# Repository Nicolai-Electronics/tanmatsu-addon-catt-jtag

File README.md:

# Tanmatsu add-on: CATT to JTAG

This repository contains the hardware design files for the CATT to JTAG adapter.

## Documentation

Need the schematic? [It's in this repository as a PDF file](schematic.pdf).

## License

This hardware design may be used under the terms of the [CERN-OHL-P](LICENSE) license.

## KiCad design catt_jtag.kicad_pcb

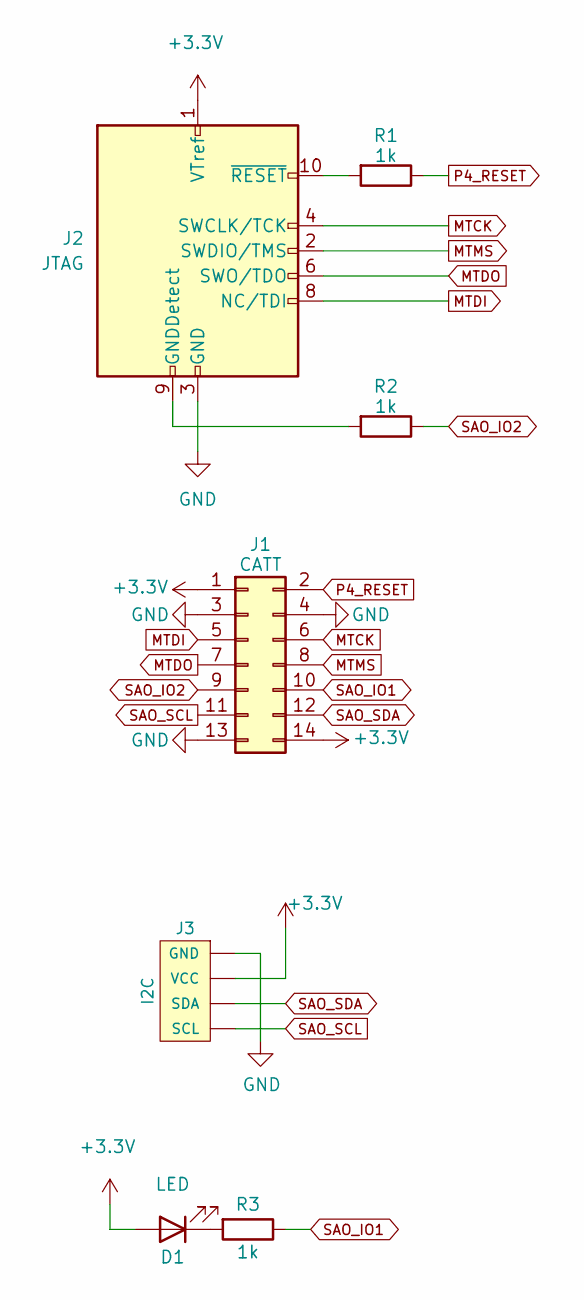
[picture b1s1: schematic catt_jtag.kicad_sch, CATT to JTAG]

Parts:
D1: LED; LED_0603_1608Metric; LCSC C7496820
J1: CATT; PinHeader_2x07_P2.54mm_Horizontal; LCSC C492435
J2: JTAG; CONN-TH_3130-10SG0BK00T1; LCSC C42372547
J3: I2C; 1X04_1MM_RA_GND; LCSC C7433425
R1, R2, R3: 1k; R_0402_1005Metric; LCSC C11702

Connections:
+3.3V: D1.2 (A), J1.1, J1.14, J2.1 (VTref), J3.2 (VCC)
GND: J1.3, J1.4, J1.13, J2.3 (GND), J2.5 (GND), J3.1 (GND), J3.5, J3.6
MTCK: J1.6, J2.4 (SWCLK/TCK)
MTDI: J1.5, J2.8 (NC/TDI)
MTDO: J1.7, J2.6 (SWO/TDO)
MTMS: J1.8, J2.2 (SWDIO/TMS)
unnamed: D1.1 (K), R3.2
unnamed: J2.9 (GNDDetect), R2.2
unnamed: J2.10 (~RESET), R1.2
P4_RESET: J1.2, R1.1
SAO_IO1: J1.10, R3.1
SAO_IO2: J1.9, R2.1
SAO_SCL: J1.11, J3.4 (SCL)
SAO_SDA: J1.12, J3.3 (SDA)

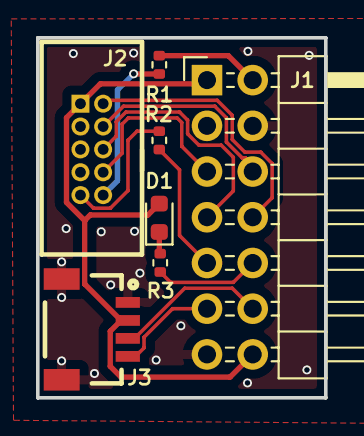
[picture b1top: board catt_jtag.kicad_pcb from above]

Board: 2 copper layers, 16.0 x 20.0 mm, 7 parts (0 on the bottom side), 14 nets.

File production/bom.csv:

Designator,Footprint,Quantity,Value,LCSC Part #
D1,0603,1,LED,C7496820
J1,PinHeader_2x07_P2.54mm_Horizontal,1,CATT,C492435
J2,CONN-TH_3130-10SG0BK00T1,1,JTAG,C42372547
J3,1X04_1MM_RA_GND,1,I2C,C7433425
"R1, R2, R3",0402,3,1k,C11702

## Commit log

2025-05-13 Update files to new Kicad version and regenerate production files
2025-05-13 Choose new components
